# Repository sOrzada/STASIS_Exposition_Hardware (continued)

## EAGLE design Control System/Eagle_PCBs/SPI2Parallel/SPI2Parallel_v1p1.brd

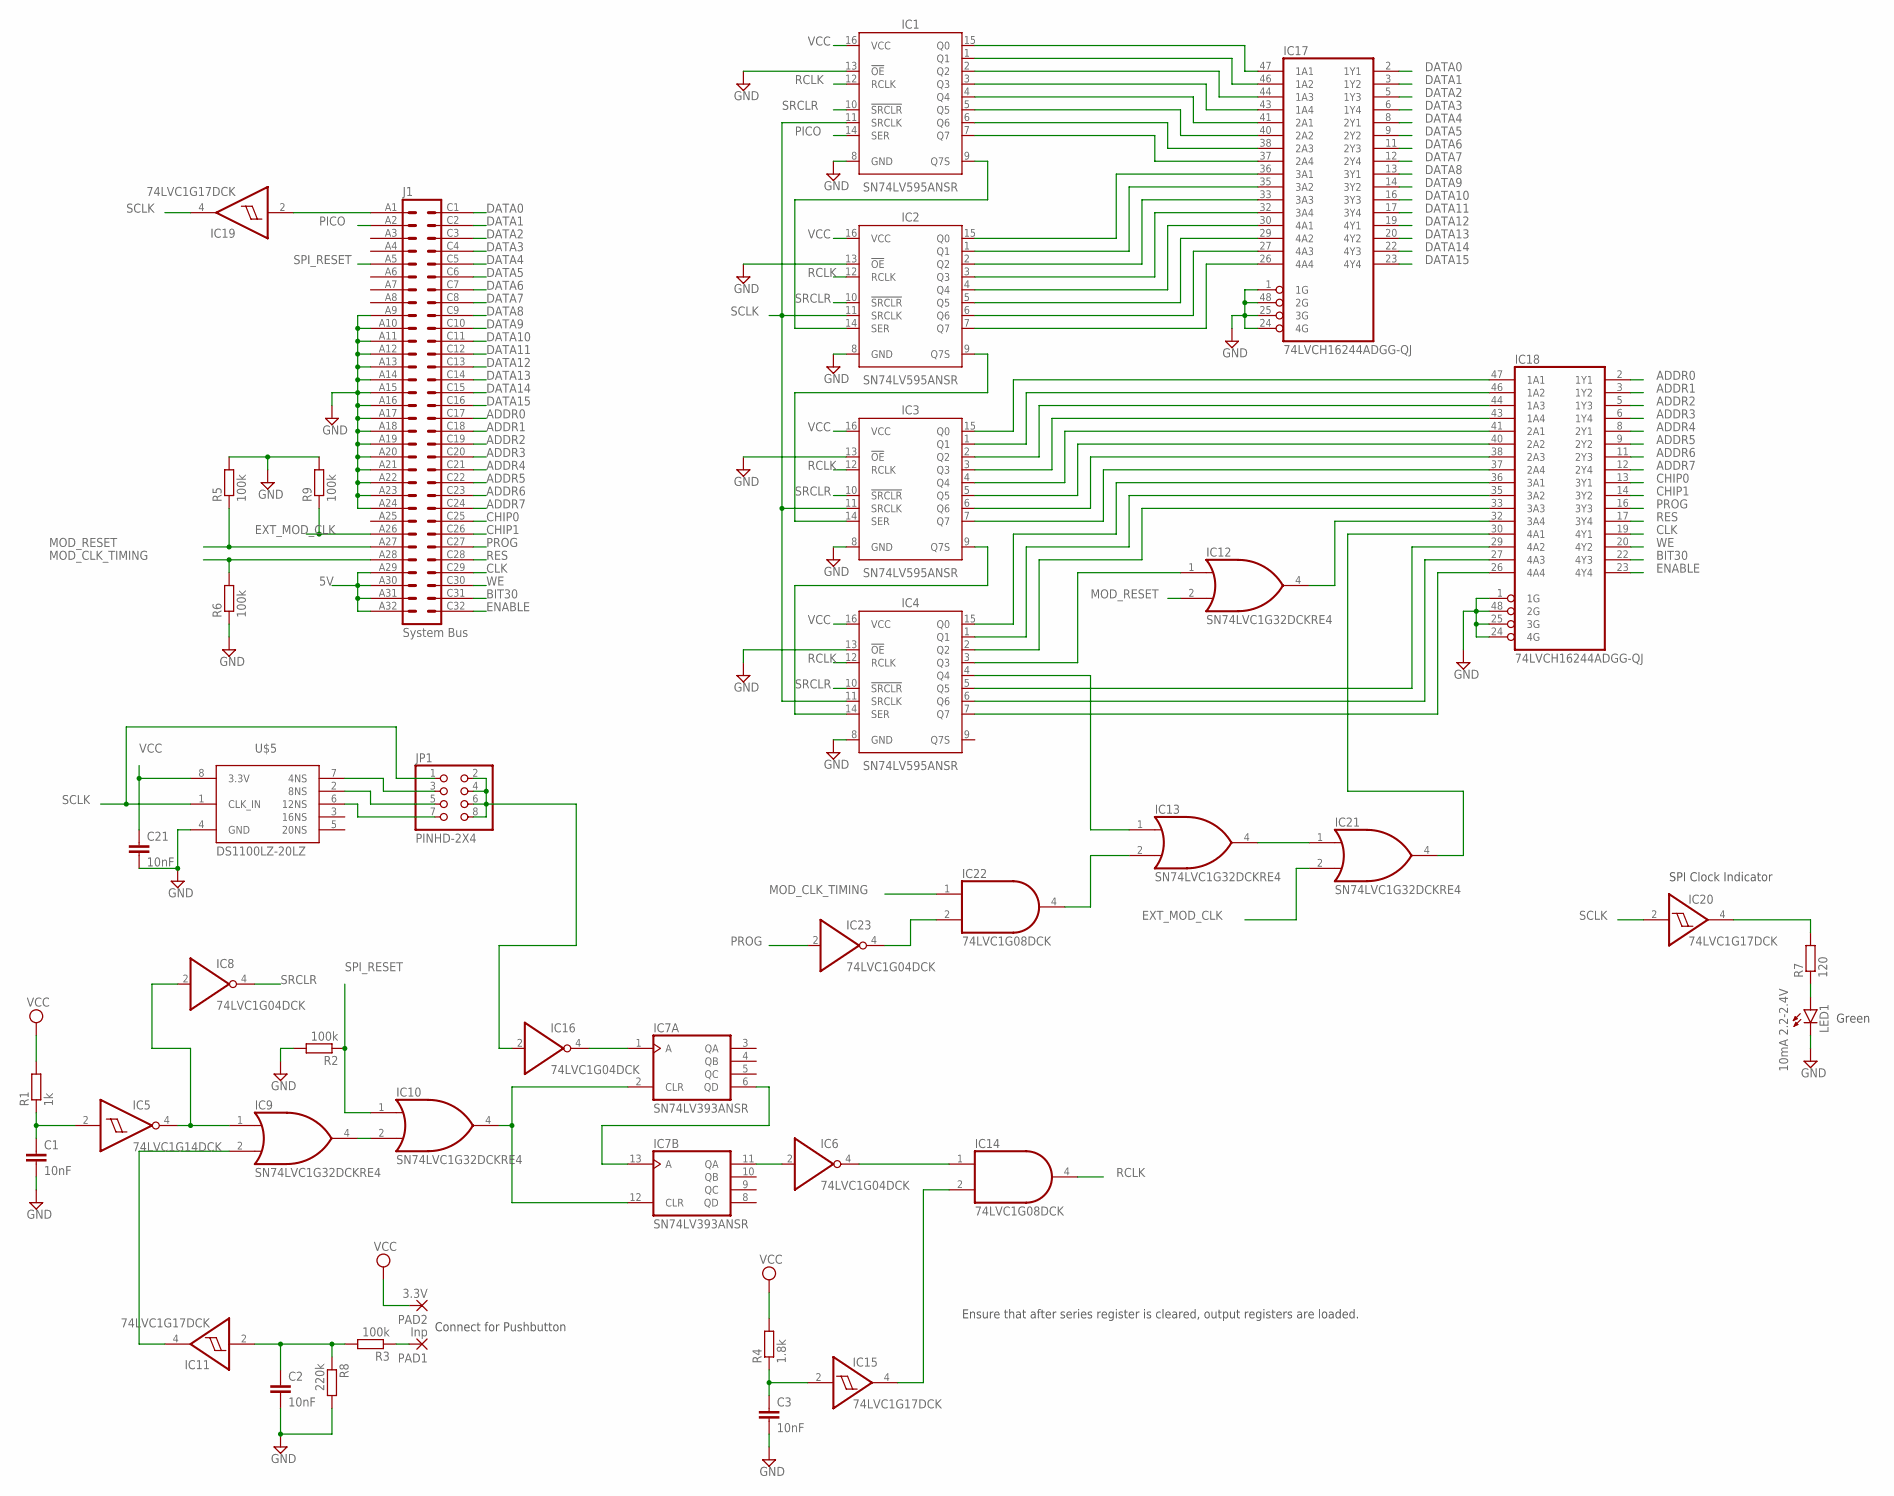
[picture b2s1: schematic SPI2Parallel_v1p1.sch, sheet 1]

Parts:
C1, C2, C3, C21: 10nF; C0603
IC1, IC2, IC3, IC4: SN74LV595ANSR; SOIC127P600X175-16N
IC5: 74LVC1G14DCK; SC70-5
IC6, IC8, IC16, IC23: 74LVC1G04DCK; SC70-5
IC7: SN74LV393ANSR; SO14
IC9, IC10, IC12, IC13, IC21: SN74LVC1G32DCKRE4; SC70-5
IC11, IC15, IC19, IC20: 74LVC1G17DCK; SC70-5
IC14, IC22: 74LVC1G08DCK; SC70-5
IC17, IC18: 74LVCH16244ADGG-QJ; SSOP48DL
J1: System Bus; VG64P
JP1: PINHD-2X4; 2X04
LED1: 10mA 2.2-2.4V; LED3MM
PAD1: Inp; SMD2,54-5,08
PAD2: 3.3V; SMD2,54-5,08
R1: 1k; R0603
R2, R3, R5, R6, R9: 100k; R0603
R4: 1.8k; R0603
R7: 120; R0603
R8: 220k; R0603
U$5: DS1100LZ-20LZ; SO-08

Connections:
5V: J1.A29, J1.A30, J1.A31, J1.A32; also elsewhere on the board
ADDR0: IC18.2 (1Y1), J1.C17
ADDR1: IC18.3 (1Y2), J1.C18
ADDR2: IC18.5 (1Y3), J1.C19
ADDR3: IC18.6 (1Y4), J1.C20
ADDR4: IC18.8 (2Y1), J1.C21
ADDR5: IC18.9 (2Y2), J1.C22
ADDR6: IC18.11 (2Y3), J1.C23
ADDR7: IC18.12 (2Y4), J1.C24
BIT30: IC18.22 (4Y3), J1.C31
CHIP0: IC18.13 (3Y1), J1.C25
CHIP1: IC18.14 (3Y2), J1.C26
CLK: IC18.19 (4Y1), J1.C29
DATA0: IC17.2 (1Y1), J1.C1
DATA1: IC17.3 (1Y2), J1.C2
DATA2: IC17.5 (1Y3), J1.C3
DATA3: IC17.6 (1Y4), J1.C4
DATA4: IC17.8 (2Y1), J1.C5
DATA5: IC17.9 (2Y2), J1.C6
DATA6: IC17.11 (2Y3), J1.C7
DATA7: IC17.12 (2Y4), J1.C8
DATA8: IC17.13 (3Y1), J1.C9
DATA9: IC17.14 (3Y2), J1.C10
DATA10: IC17.16 (3Y3), J1.C11
DATA11: IC17.17 (3Y4), J1.C12
DATA12: IC17.19 (4Y1), J1.C13
DATA13: IC17.20 (4Y2), J1.C14
DATA14: IC17.22 (4Y3), J1.C15
DATA15: IC17.23 (4Y4), J1.C16
ENABLE: IC18.23 (4Y4), J1.C32
EXT_MOD_CLK: IC21.2 (I1), J1.A26, R9.1
GND: C1.2, C2.2, C3.2, C21.2, IC1.8 (GND), IC1.13 (!OE), IC2.8 (GND), IC2.13 (!OE), IC3.8 (GND), IC3.13 (!OE), IC4.8 (GND), IC4.13 (!OE), IC5.3 (GND), IC6.3 (GND), IC7.7 (GND), IC8.3 (GND), IC9.3 (GND), IC10.3 (GND), IC11.3 (GND), IC12.3 (GND), IC13.3 (GND), IC14.3 (GND), IC15.3 (GND), IC16.3 (GND), IC17.1 (1G), IC17.4 (GND), IC17.10 (GND), IC17.15 (GND), IC17.21 (GND), IC17.24 (4G), IC17.25 (3G), IC17.28 (GND), IC17.34 (GND), IC17.39 (GND), IC17.45 (GND), IC17.48 (2G), IC18.1 (1G), IC18.4 (GND), IC18.10 (GND), IC18.15 (GND), IC18.21 (GND), IC18.24 (4G), IC18.25 (3G), IC18.28 (GND), IC18.34 (GND), IC18.39 (GND), IC18.45 (GND), IC18.48 (2G), IC19.3 (GND), IC20.3 (GND), IC21.3 (GND), IC22.3 (GND), IC23.3 (GND), J1.A9, J1.A10, J1.A11, J1.A12, J1.A13, J1.A14, J1.A15, J1.A16, J1.A17, J1.A18, J1.A19, J1.A20, J1.A21, J1.A22, J1.A23, J1.A24, LED1.K (C), R2.2, R5.2, R6.1, R8.2, R9.2, U$5.4 (GND); also elsewhere on the board
MOD_CLK_TIMING: IC22.1 (I0), J1.A28, R6.2
MOD_RESET: IC12.2 (I1), J1.A27, R5.1
unnamed: IC1.9 (Q7S), IC2.14 (SER)
unnamed: IC2.9 (Q7S), IC3.14 (SER)
unnamed: IC3.9 (Q7S), IC4.14 (SER)
unnamed: IC7.6 (QD), IC7.13 (A)
unnamed: IC6.2 (I), IC7.11 (QA)
unnamed: C1.1, IC5.2 (I), R1.1
unnamed: IC7.2 (CLR), IC7.12 (CLR), IC10.4 (O)
unnamed: IC9.4 (O), IC10.2 (I1)
unnamed: IC5.4 (O), IC8.2 (I), IC9.1 (I0)
unnamed: C2.1, IC11.2 (I), R3.2, R8.1
unnamed: IC9.2 (I1), IC11.4 (O)
unnamed: PAD1.1, R3.1
unnamed: IC4.3 (Q3), IC12.1 (I0)
unnamed: IC4.4 (Q4), IC13.1 (I0)
unnamed: IC6.4 (O), IC14.1 (I0)
unnamed: C3.1, IC15.2 (I), R4.1
unnamed: IC14.2 (I1), IC15.4 (O)
unnamed: IC7.1 (A), IC16.4 (O)
unnamed: IC1.15 (Q0), IC17.47 (1A1)
unnamed: IC1.1 (Q1), IC17.46 (1A2)
unnamed: IC1.2 (Q2), IC17.44 (1A3)
unnamed: IC1.3 (Q3), IC17.43 (1A4)
unnamed: IC1.4 (Q4), IC17.41 (2A1)
unnamed: IC1.5 (Q5), IC17.40 (2A2)
unnamed: IC1.6 (Q6), IC17.38 (2A3)
unnamed: IC1.7 (Q7), IC17.37 (2A4)
unnamed: IC2.15 (Q0), IC17.36 (3A1)
unnamed: IC2.1 (Q1), IC17.35 (3A2)
unnamed: IC2.2 (Q2), IC17.33 (3A3)
unnamed: IC2.3 (Q3), IC17.32 (3A4)
unnamed: IC2.4 (Q4), IC17.30 (4A1)
unnamed: IC2.5 (Q5), IC17.29 (4A2)
unnamed: IC2.6 (Q6), IC17.27 (4A3)
unnamed: IC2.7 (Q7), IC17.26 (4A4)
unnamed: IC3.15 (Q0), IC18.47 (1A1)
unnamed: IC3.1 (Q1), IC18.46 (1A2)
unnamed: IC3.2 (Q2), IC18.44 (1A3)
unnamed: IC3.3 (Q3), IC18.43 (1A4)
unnamed: IC3.4 (Q4), IC18.41 (2A1)
unnamed: IC3.5 (Q5), IC18.40 (2A2)
unnamed: IC3.6 (Q6), IC18.38 (2A3)
unnamed: IC3.7 (Q7), IC18.37 (2A4)
unnamed: IC4.15 (Q0), IC18.36 (3A1)
unnamed: IC4.1 (Q1), IC18.35 (3A2)
unnamed: IC4.2 (Q2), IC18.33 (3A3)
unnamed: IC12.4 (O), IC18.32 (3A4)
unnamed: IC18.30 (4A1), IC21.4 (O)
unnamed: IC4.5 (Q5), IC18.29 (4A2)
unnamed: IC4.6 (Q6), IC18.27 (4A3)
unnamed: IC4.7 (Q7), IC18.26 (4A4)
unnamed: IC16.2 (I), JP1.2, JP1.4, JP1.6, JP1.8
unnamed: JP1.7, U$5.6 (12NS)
unnamed: JP1.3, U$5.7 (4NS)
unnamed: JP1.5, U$5.2 (8NS)
unnamed: IC19.2 (I), J1.A1
unnamed: IC13.4 (O), IC21.1 (I0)
unnamed: IC13.2 (I1), IC22.4 (O)
unnamed: IC22.2 (I1), IC23.4 (O)
unnamed: IC20.4 (O), R7.2
unnamed: LED1.A, R7.1
PICO: IC1.14 (SER), J1.A2
PROG: IC18.16 (3Y3), IC23.2 (I), J1.C27
RCLK: IC1.12 (RCLK), IC2.12 (RCLK), IC3.12 (RCLK), IC4.12 (RCLK), IC14.4 (O)
RES: IC18.17 (3Y4), J1.C28
SCLK: IC1.11 (SRCLK), IC2.11 (SRCLK), IC3.11 (SRCLK), IC4.11 (SRCLK), IC19.4 (O), IC20.2 (I), JP1.1, U$5.1 (CLK_IN)
SPI_RESET: IC10.1 (I0), J1.A5, R2.1
SRCLR: IC1.10 (!SRCLR), IC2.10 (!SRCLR), IC3.10 (!SRCLR), IC4.10 (!SRCLR), IC8.4 (O)
VCC: C21.1, IC1.16 (VCC), IC2.16 (VCC), IC3.16 (VCC), IC4.16 (VCC), IC5.5 (VCC), IC6.5 (VCC), IC7.14 (VCC), IC8.5 (VCC), IC9.5 (VCC), IC10.5 (VCC), IC11.5 (VCC), IC12.5 (VCC), IC13.5 (VCC), IC14.5 (VCC), IC15.5 (VCC), IC16.5 (VCC), IC17.7 (VCC), IC17.18 (VCC), IC17.31 (VCC), IC17.42 (VCC), IC18.7 (VCC), IC18.18 (VCC), IC18.31 (VCC), IC18.42 (VCC), IC19.5 (VCC), IC20.5 (VCC), IC21.5 (VCC), IC22.5 (VCC), IC23.5 (VCC), PAD2.1, R1.2, R4.2, U$5.8 (3.3V); also elsewhere on the board
WE: IC18.20 (4Y2), J1.C30

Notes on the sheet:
Connect for Pushbutton
Ensure that after series register is cleared, output registers are loaded.
Green
SPI Clock Indicator

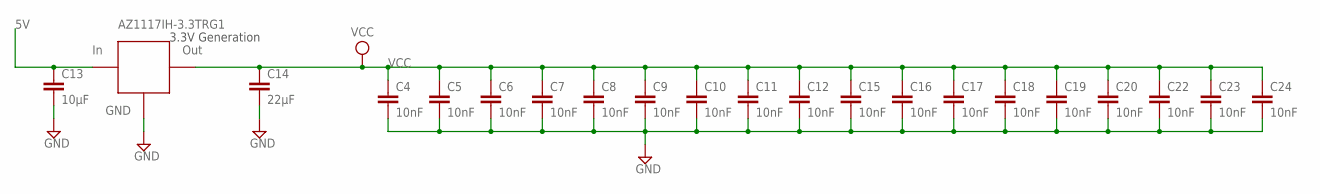
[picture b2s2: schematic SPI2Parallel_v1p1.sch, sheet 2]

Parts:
C4, C5, C6, C7, C8, C9, C10, C11, C12, C15, C16, C17, C18, C19, C20, C22, C23, C24: 10nF; C0603
C13: 10µF; C1206
C14: 22µF; C1206
U$9: AZ1117IH-3.3TRG1; SOT223

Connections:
5V: C13.1, U$9.3 (IN); also elsewhere on the board
GND: C4.2, C5.2, C6.2, C7.2, C8.2, C9.2, C10.2, C11.2, C12.2, C13.2, C14.2, C15.2, C16.2, C17.2, C18.2, C19.2, C20.2, C22.2, C23.2, C24.2, U$9.1 (GND); also elsewhere on the board
VCC: C4.1, C5.1, C6.1, C7.1, C8.1, C9.1, C10.1, C11.1, C12.1, C14.1, C15.1, C16.1, C17.1, C18.1, C19.1, C20.1, C22.1, C23.1, C24.1, U$9.2 (VCC), U$9.4 (VCC); also elsewhere on the board

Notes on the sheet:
3.3V Generation

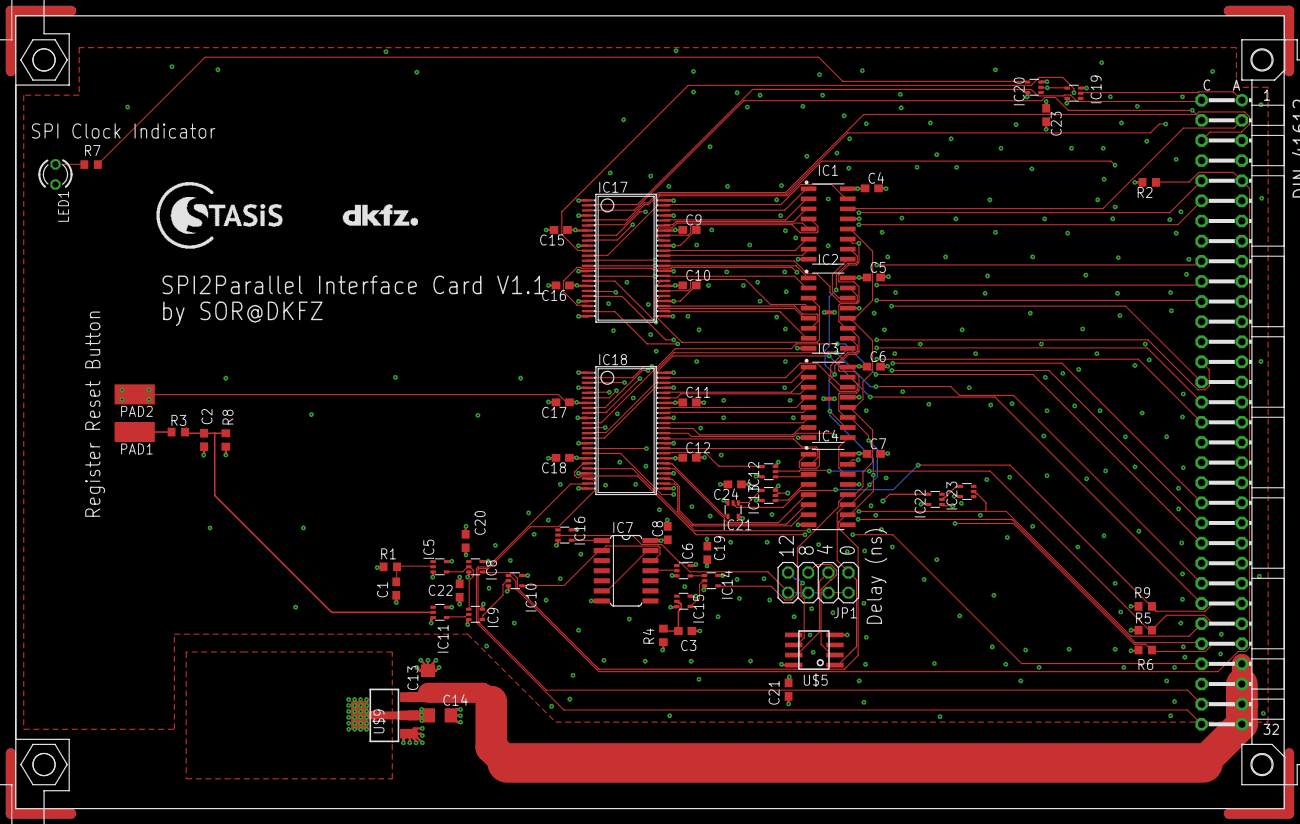
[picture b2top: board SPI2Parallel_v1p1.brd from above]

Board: 4 copper layers, 160.0 x 100.0 mm, 65 parts (0 on the bottom side), 103 nets.

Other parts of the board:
U$1: LOGO_STASIS
U$2: LOGO_DKFZ

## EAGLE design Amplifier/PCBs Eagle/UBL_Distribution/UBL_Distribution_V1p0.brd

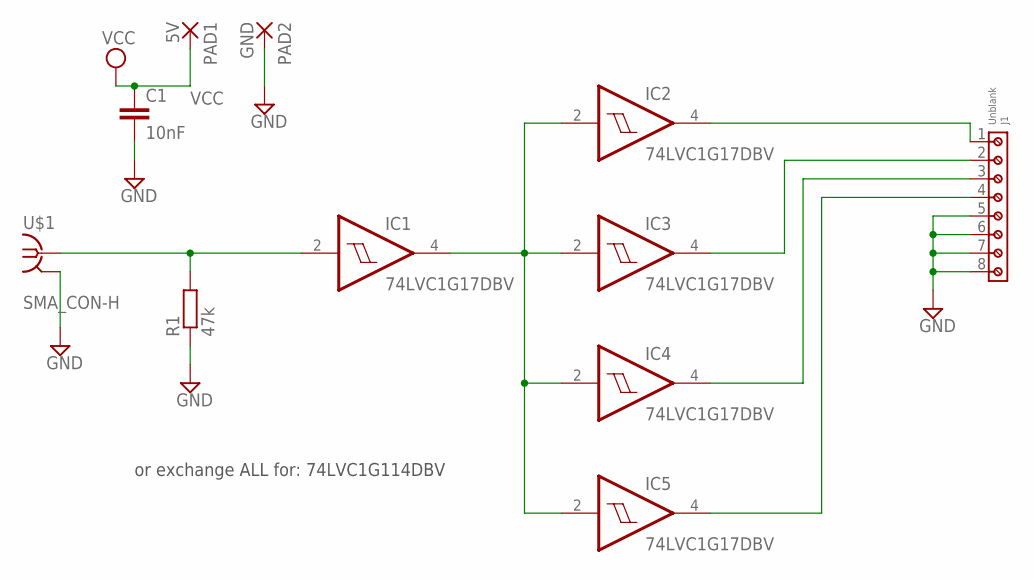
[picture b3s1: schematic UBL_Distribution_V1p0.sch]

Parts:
C1: 10nF; C0805
IC1, IC2, IC3, IC4, IC5: 74LVC1G17DBV; SOT23-5
J1: Unblank; 691210910008
PAD1: 5V; SMD2,54-5,08
PAD2: GND; SMD2,54-5,08
R1: 47k; R0805
U$1: SMA_CON-H; BU-SMA-H

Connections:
GND: C1.2, IC1.3 (GND), IC2.3 (GND), IC3.3 (GND), IC4.3 (GND), IC5.3 (GND), J1.5, J1.6, J1.7, J1.8, PAD2.1, R1.1, U$1.2 (GND), U$1.3 (GND), U$1.4 (GND), U$1.5 (GND)
unnamed: IC1.2 (I), R1.2, U$1.1
unnamed: IC1.4 (O), IC2.2 (I), IC3.2 (I), IC4.2 (I), IC5.2 (I)
unnamed: IC2.4 (O), J1.1
unnamed: IC3.4 (O), J1.2
unnamed: IC4.4 (O), J1.3
unnamed: IC5.4 (O), J1.4
VCC: C1.1, IC1.5 (VCC), IC2.5 (VCC), IC3.5 (VCC), IC4.5 (VCC), IC5.5 (VCC), PAD1.1

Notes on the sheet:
or exchange ALL for: 74LVC1G114DBV

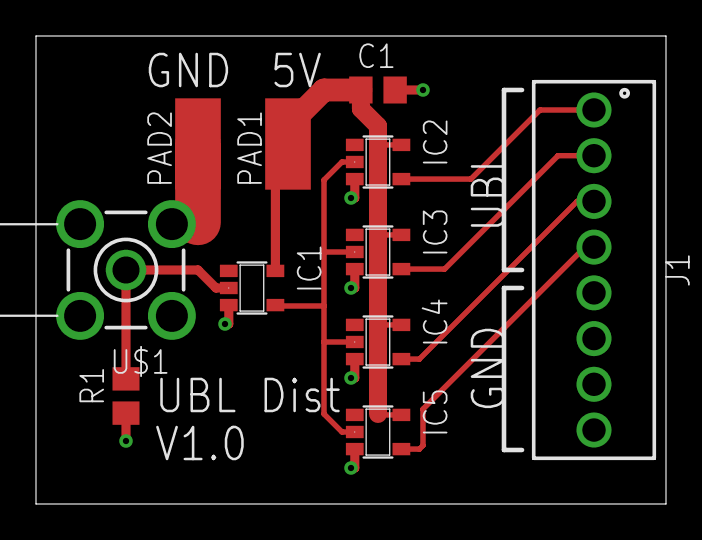
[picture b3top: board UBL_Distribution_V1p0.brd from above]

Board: 2 copper layers, 35.0 x 26.0 mm, 11 parts (0 on the bottom side), 8 nets.

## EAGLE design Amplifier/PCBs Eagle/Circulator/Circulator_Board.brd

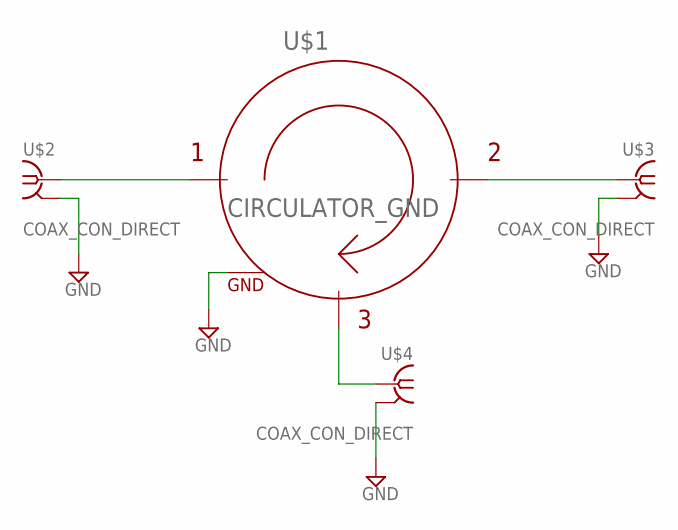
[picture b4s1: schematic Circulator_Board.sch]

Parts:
U$1: CIRCULATOR_GND; JCD0126T0130LC100
U$2, U$3, U$4: COAX_CON_DIRECT; COAX.141

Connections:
GND: U$1.P$1 (P$GND), U$1.P$2 (P$GND), U$1.P$3 (P$GND), U$1.P$4 (P$GND), U$2.P$2 (GND), U$3.P$2 (GND), U$4.P$2 (GND)
unnamed: U$1.P$IN, U$2.P$1 (1)
unnamed: U$1.P$OUT, U$3.P$1 (1)
unnamed: U$1.P$LOAD, U$4.P$1 (1)

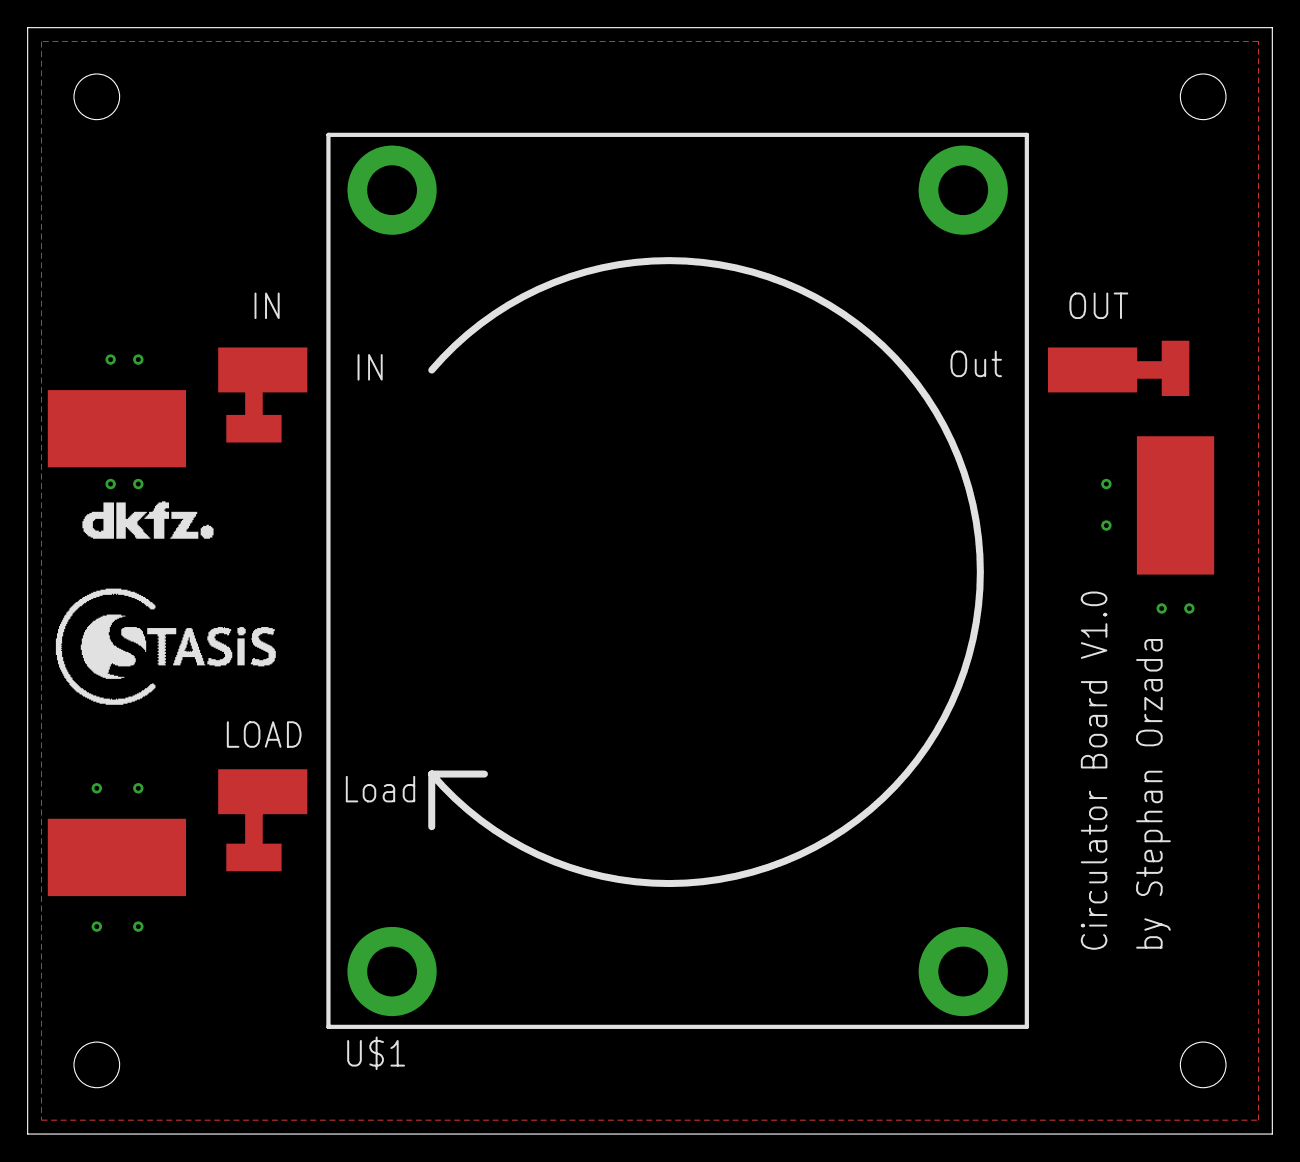
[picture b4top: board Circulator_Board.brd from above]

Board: 2 copper layers, 90.0 x 80.0 mm, 6 parts (0 on the bottom side), 4 nets.

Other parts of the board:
U$5: LOGO_DKFZ
U$6: LOGO_STASIS

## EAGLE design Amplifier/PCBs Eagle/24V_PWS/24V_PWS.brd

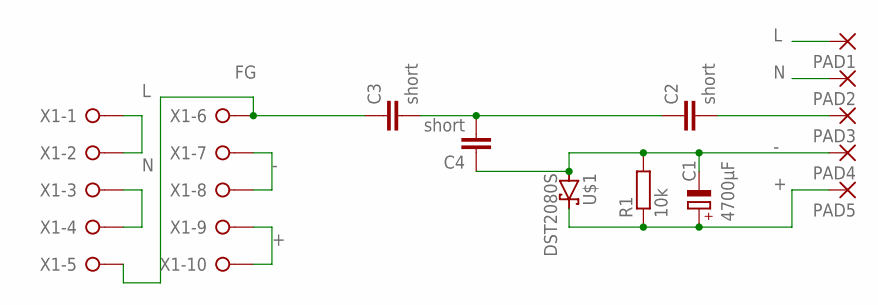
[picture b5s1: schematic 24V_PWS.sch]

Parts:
C1: 4700µF; E7,5-18
C2, C3, C4: short; C1206
PAD1, PAD2, PAD3, PAD4, PAD5: SMD5; SMD2,54-5,08
R1: 10k; R2012
U$1: DST2080S; TO-277B
X1: W237-10P

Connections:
+: C1.+, PAD5.1, R1.1, U$1.P$1 (C), X1.9, X1.10
-: C1.-, C4.1, PAD4.1, R1.2, U$1.P$2 (A), U$1.P$3 (A), X1.7, X1.8
FG: C3.1, X1.5, X1.6
L: PAD1.1, X1.1, X1.2
N: PAD2.1, X1.3, X1.4
unnamed: C2.2, PAD3.1
unnamed: C2.1, C3.2, C4.2

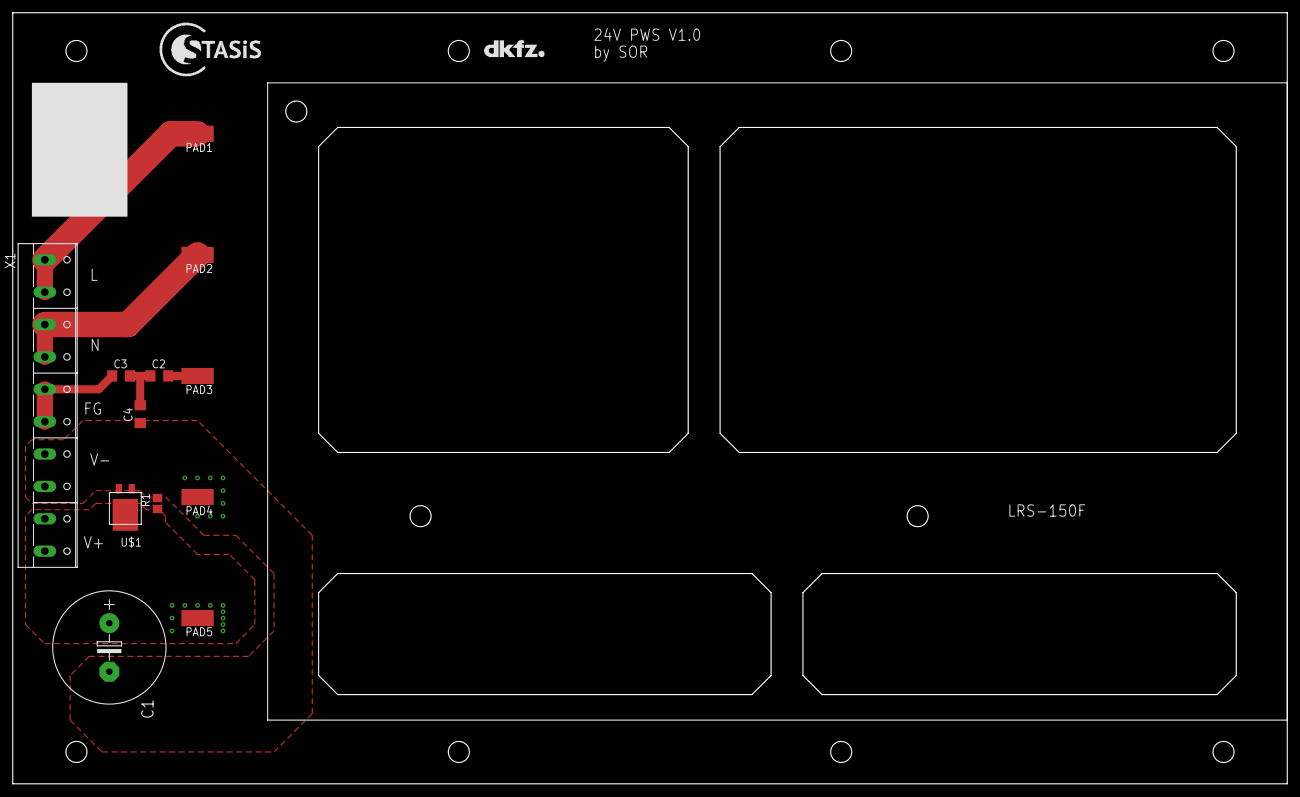
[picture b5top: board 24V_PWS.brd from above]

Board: 2 copper layers, 200.0 x 121.0 mm, 14 parts (0 on the bottom side), 7 nets.

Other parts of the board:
U$2: LOGO_STASIS
U$3: LOGO_DKFZ

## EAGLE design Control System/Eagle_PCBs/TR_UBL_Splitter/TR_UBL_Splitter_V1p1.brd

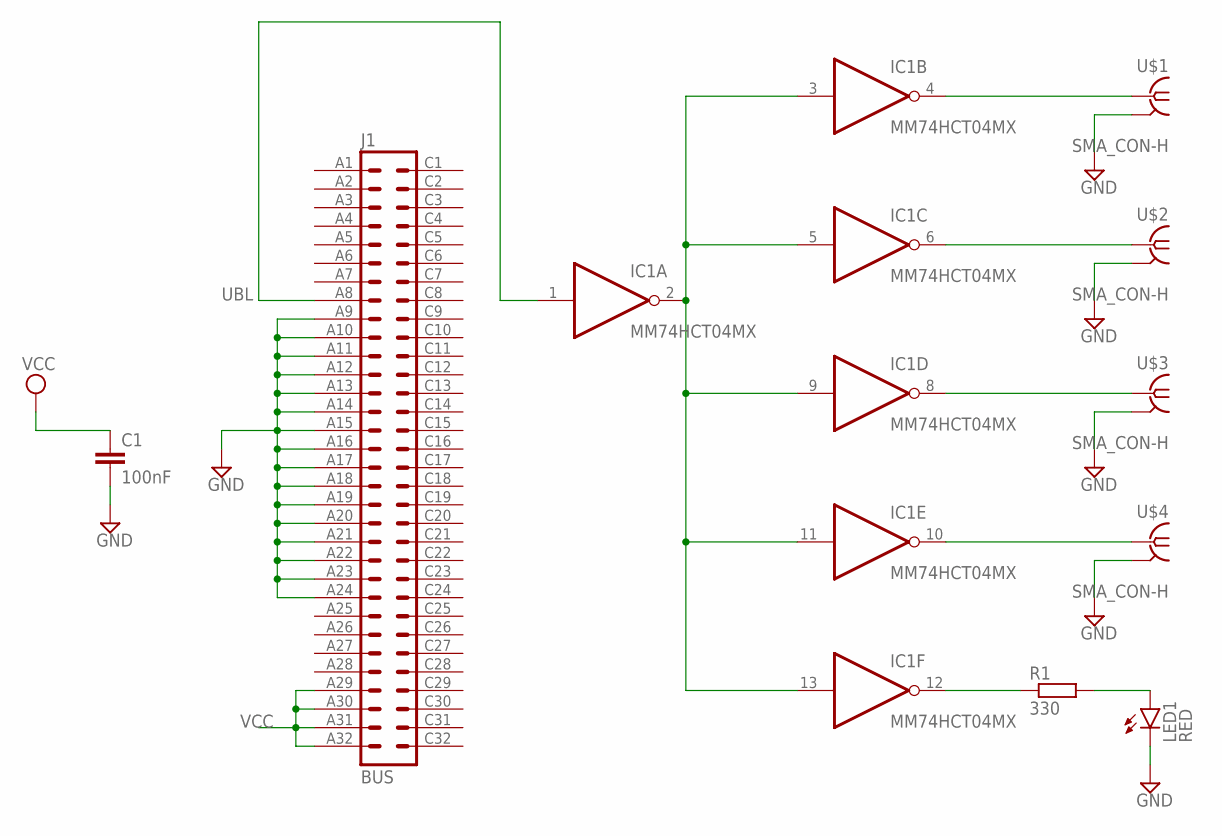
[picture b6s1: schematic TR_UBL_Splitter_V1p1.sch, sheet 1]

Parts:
C1: 100nF; C0603
IC1: MM74HCT04MX; SO14
J1: BUS; VG64P
LED1: RED; LED3MM
R1: 330; R0603
U$1, U$2, U$3, U$4: SMA_CON-H; BU-SMA-H

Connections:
GND: C1.2, IC1.7 (GND), J1.A9, J1.A10, J1.A11, J1.A12, J1.A13, J1.A14, J1.A15, J1.A16, J1.A17, J1.A18, J1.A19, J1.A20, J1.A21, J1.A22, J1.A23, J1.A24, LED1.K (C), U$1.2 (GND), U$1.3 (GND), U$1.4 (GND), U$1.5 (GND), U$2.2 (GND), U$2.3 (GND), U$2.4 (GND), U$2.5 (GND), U$3.2 (GND), U$3.3 (GND), U$3.4 (GND), U$3.5 (GND), U$4.2 (GND), U$4.3 (GND), U$4.4 (GND), U$4.5 (GND)
unnamed: IC1.2 (O), IC1.3 (I), IC1.5 (I), IC1.9 (I), IC1.11 (I), IC1.13 (I)
unnamed: IC1.4 (O), U$1.1
unnamed: LED1.A, R1.2
unnamed: IC1.6 (O), U$2.1
unnamed: IC1.12 (O), R1.1
unnamed: IC1.8 (O), U$3.1
unnamed: IC1.10 (O), U$4.1
UBL: IC1.1 (I), J1.A8
VCC: C1.1, IC1.14 (VCC), J1.A29, J1.A30, J1.A31, J1.A32

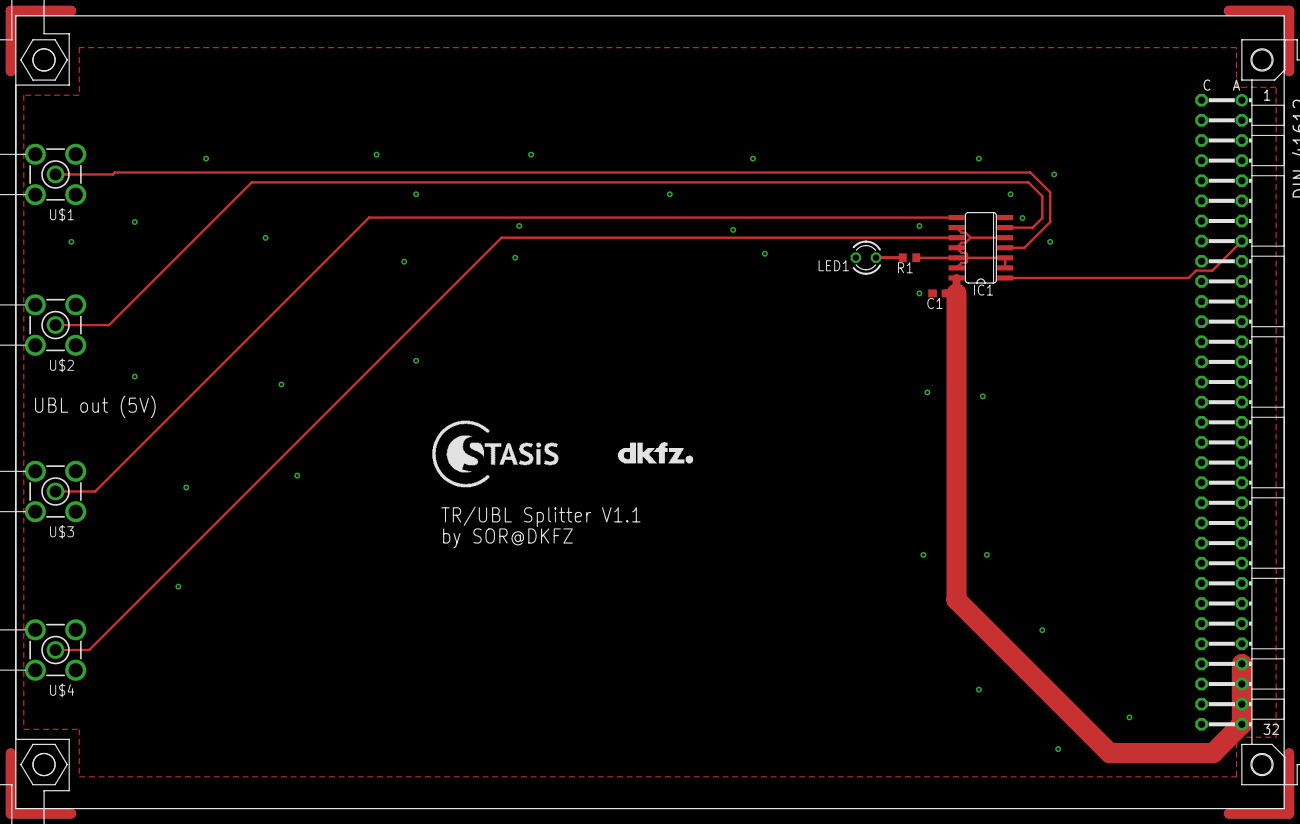
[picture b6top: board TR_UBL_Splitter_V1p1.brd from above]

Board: 2 copper layers, 160.0 x 100.0 mm, 11 parts (0 on the bottom side), 10 nets.

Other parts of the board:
U$5: LOGO_STASIS
U$6: LOGO_DKFZ

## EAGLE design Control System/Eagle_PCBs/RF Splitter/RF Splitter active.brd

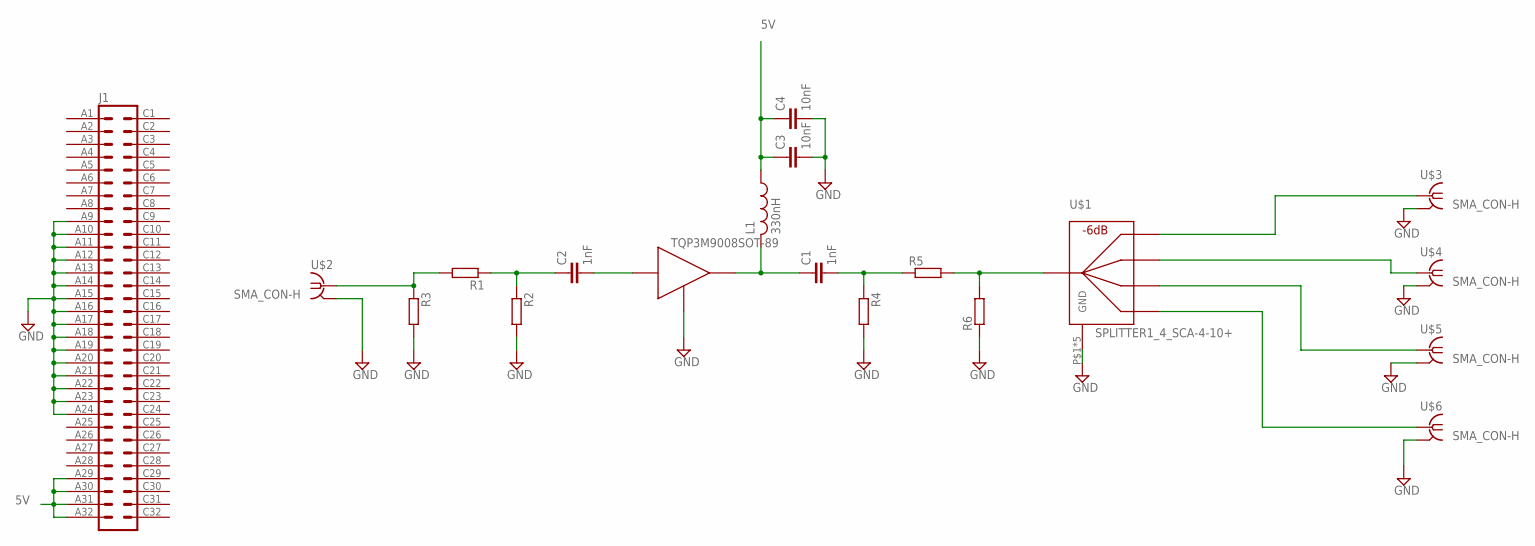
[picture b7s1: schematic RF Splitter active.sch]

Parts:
C1, C2: 1nF; C0603
C3, C4: 10nF; C0603
J1: VG64P
L1: 330nH; L2012C
R1, R2, R3, R4, R5, R6: R-EU_R0603; R0603
U$1: SPLITTER1_4_SCA-4-10+; SCA-4-10+
U$2, U$3, U$4, U$5, U$6: SMA_CON-H; BU-SMA-H
U$7: TQP3M9008SOT-89; SOT89

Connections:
5V: C3.1, C4.1, J1.A29, J1.A30, J1.A31, J1.A32, L1.1
GND: C3.2, C4.2, J1.A9, J1.A10, J1.A11, J1.A12, J1.A13, J1.A14, J1.A15, J1.A16, J1.A17, J1.A18, J1.A19, J1.A20, J1.A21, J1.A22, J1.A23, J1.A24, R2.2, R3.2, R4.2, R6.1, U$1.P$1 (GND), U$1.P$2 (GND), U$1.P$4 (GND), U$1.P$5 (GND), U$1.P$8 (GND), U$2.2 (GND), U$2.3 (GND), U$2.4 (GND), U$2.5 (GND), U$3.2 (GND), U$3.3 (GND), U$3.4 (GND), U$3.5 (GND), U$4.2 (GND), U$4.3 (GND), U$4.4 (GND), U$4.5 (GND), U$5.2 (GND), U$5.3 (GND), U$5.4 (GND), U$5.5 (GND), U$6.2 (GND), U$6.3 (GND), U$6.4 (GND), U$6.5 (GND), U$7.2 (GND), U$7.2@1 (GND)
unnamed: C2.2, U$7.1 (IN)
unnamed: U$1.P$6, U$3.1
unnamed: U$1.P$7, U$4.1
unnamed: U$1.P$9, U$5.1
unnamed: U$1.P$10, U$6.1
unnamed: C1.1, L1.2, U$7.3 (OUT)
unnamed: C1.2, R4.1, R5.1
unnamed: R5.2, R6.2, U$1.P$3
unnamed: R1.2, R3.1, U$2.1
unnamed: C2.1, R1.1, R2.1

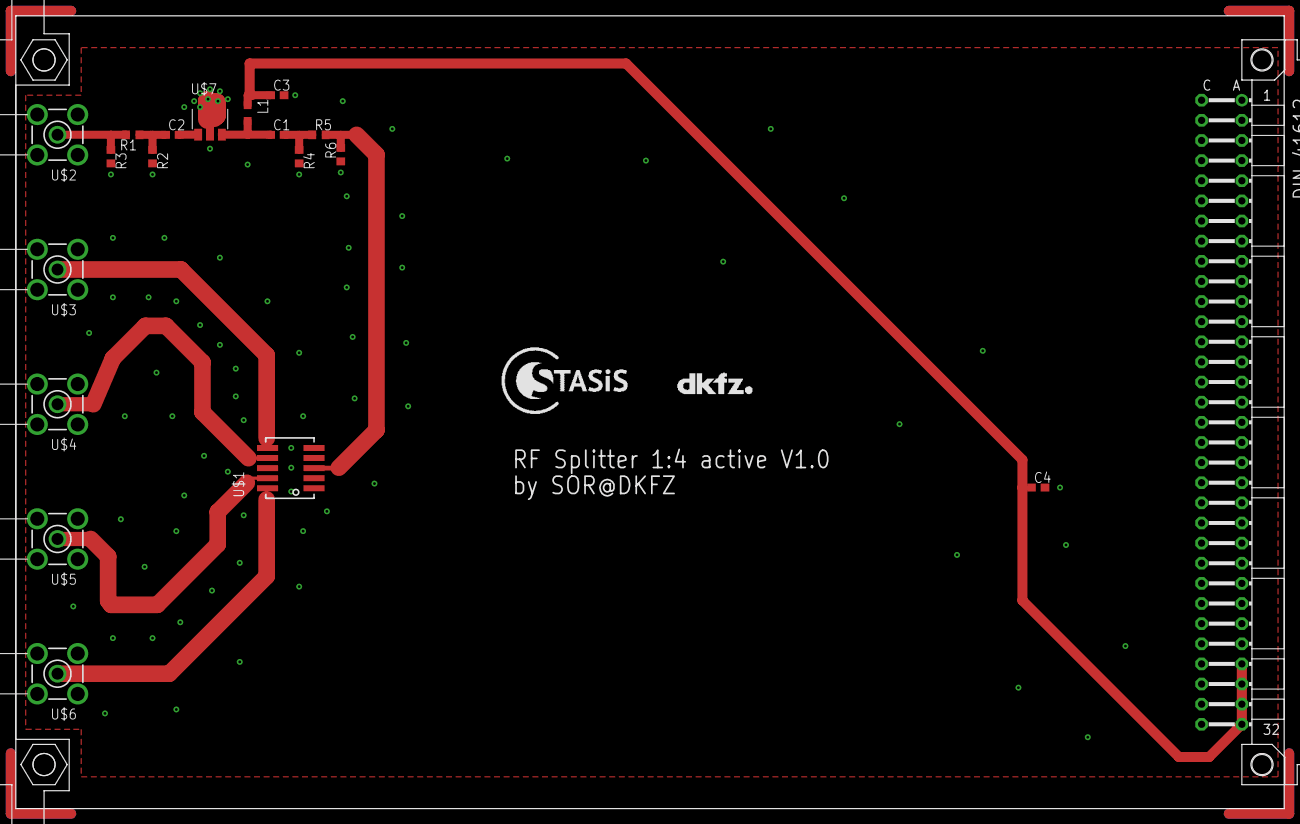
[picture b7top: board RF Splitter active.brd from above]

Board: 2 copper layers, 160.0 x 100.0 mm, 21 parts (0 on the bottom side), 12 nets.

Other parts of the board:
U$8: LOGO_STASIS
U$9: LOGO_DKFZ

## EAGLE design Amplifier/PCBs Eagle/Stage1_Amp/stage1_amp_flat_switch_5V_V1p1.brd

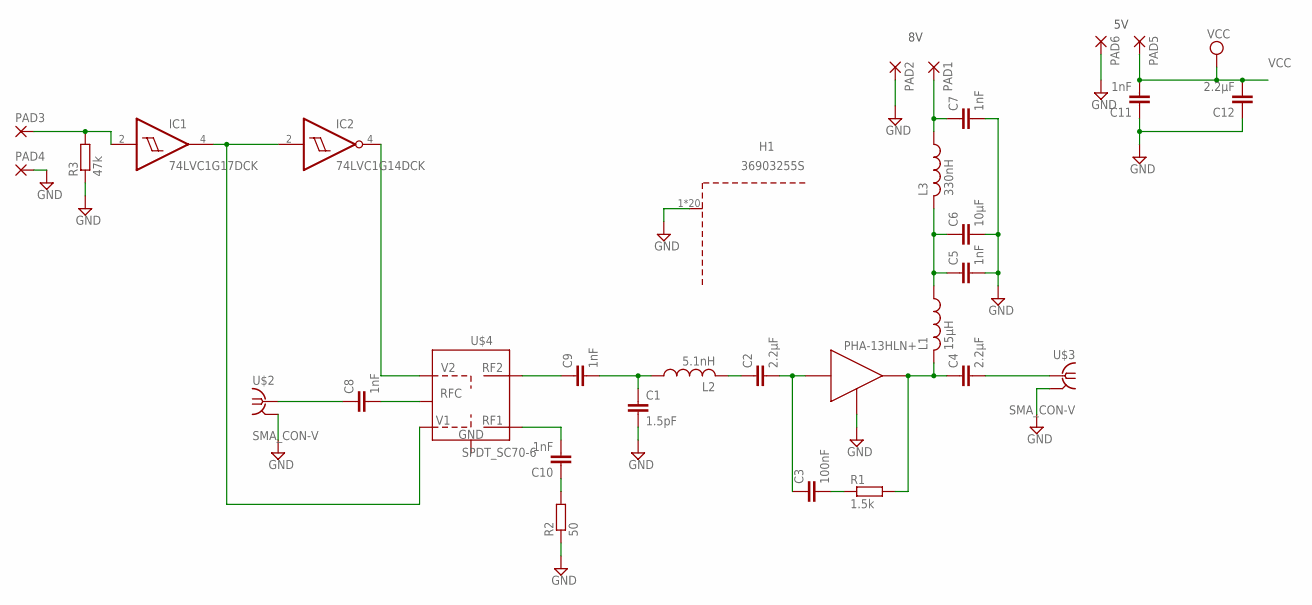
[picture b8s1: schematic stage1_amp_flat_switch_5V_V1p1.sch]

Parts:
C1: 1.5pF; C0402
C2, C4, C12: 2.2µF; C0402
C3: 100nF; C0402
C5, C7, C8, C9, C10, C11: 1nF; C0402
C6: 10µF; C0805
H1: 36903255S; WE-SHC_ONE-PIECE_36903255S
IC1: 74LVC1G17DCK; SC70-5
IC2: 74LVC1G14DCK; SC70-5
L1: 15µH; L3225M
L2: 5.1nH; L2012C
L3: 330nH; L3225M
PAD1, PAD2, PAD3, PAD4, PAD5, PAD6: SMD5; SMD2,54-5,08
R1: 1.5k; R0402
R2: 50; R0402
R3: 47k; R0805
U$1: PHA-13HLN+; SOT89
U$2, U$3: SMA_CON-V; BU-SMA-V
U$4: SPDT_SC70-6; SC70-6

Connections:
GND: C1.2, C5.2, C6.2, C7.2, C11.1, C12.1, H1.1, H1.2, H1.3, H1.4, H1.5, H1.6, H1.7, H1.8, H1.9, H1.10, H1.11, H1.12, H1.13, H1.14, H1.15, H1.16, H1.17, H1.18, H1.19, H1.20, IC1.3 (GND), IC2.3 (GND), PAD2.1, PAD4.1, PAD6.1, R2.1, R3.1, U$1.2 (GND), U$1.2@1 (GND), U$2.2 (GND), U$2.3 (GND), U$2.4 (GND), U$2.5 (GND), U$3.2 (GND), U$3.3 (GND), U$3.4 (GND), U$3.5 (GND)
unnamed: C2.1, L2.2
unnamed: C2.2, C3.1, U$1.1 (IN)
unnamed: C4.1, L1.2, R1.2, U$1.3 (OUT)
unnamed: C1.1, C9.2, L2.1
unnamed: C3.2, R1.1
unnamed: C4.2, U$3.1
unnamed: C5.1, C6.1, L1.1, L3.2
unnamed: C7.1, L3.1, PAD1.1
unnamed: C8.2, U$4.5 (RFC)
unnamed: C8.1, U$2.1
unnamed: C9.1, U$4.3 (RF2)
unnamed: C10.2, U$4.1 (RF1)
unnamed: C10.1, R2.2
unnamed: IC1.4 (O), IC2.2 (I), U$4.6 (V1)
unnamed: IC2.4 (O), U$4.4 (V2)
unnamed: IC1.2 (I), PAD3.1, R3.2
VCC: C11.2, C12.2, IC1.5 (VCC), IC2.5 (VCC), PAD5.1

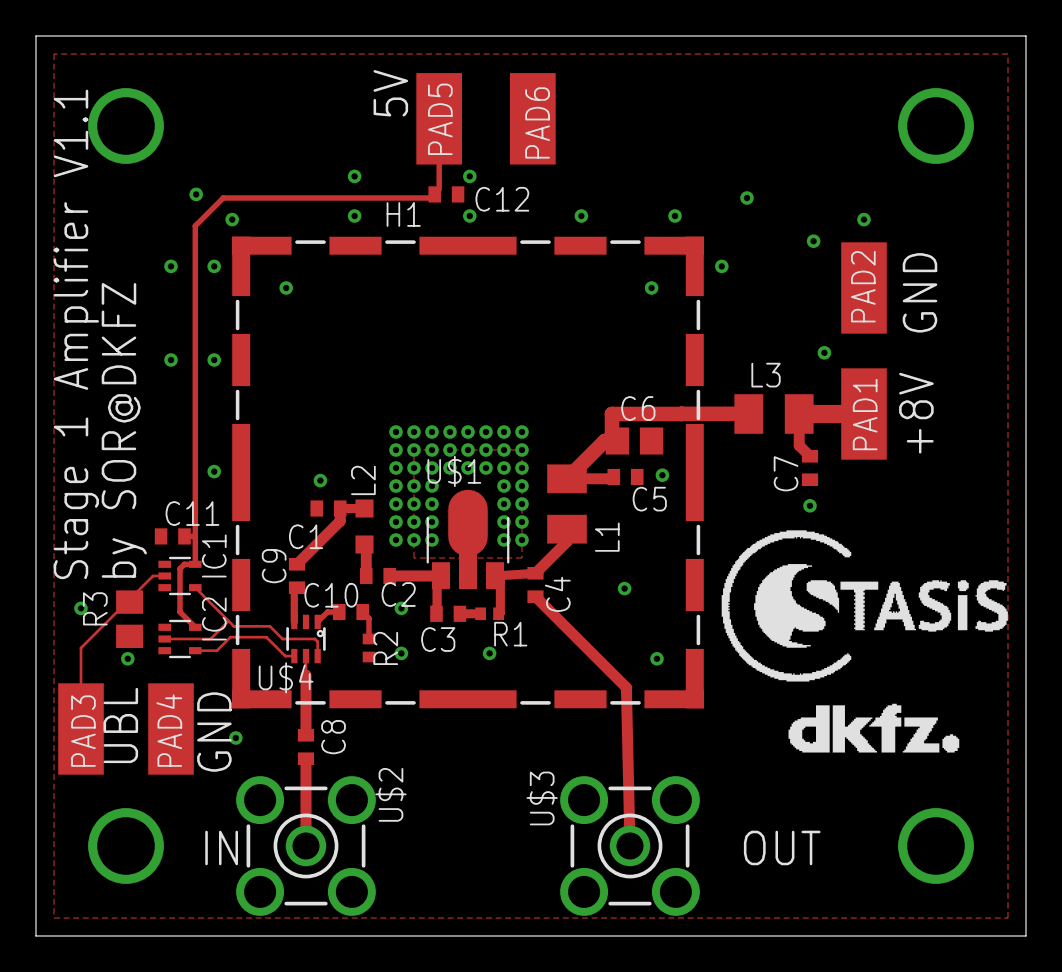
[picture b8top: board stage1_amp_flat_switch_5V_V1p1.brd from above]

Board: 2 copper layers, 55.0 x 50.0 mm, 33 parts (0 on the bottom side), 18 nets.

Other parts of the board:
U$5: LOGO_DKFZ
U$6: LOGO_STASIS

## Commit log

2025-02-12 Upload Array data and Main Documentation Document.
2025-02-12 Upload PCBs and Housing
2025-02-12 Deleted Backup of Documentation Document.
2025-02-12 Added Name to Readme
2025-02-12 Changed Readme
2025-02-12 Added Spice Simulations
    -HPA
    -2nd stage amplifier
    -Voltage Control
2025-02-12 Create LICENSE
    Added License
2025-02-12 Create Disclaimer.txt
    Created disclaimer.
2025-02-12 Closed KiCad, which changed a backup file.
2025-02-17 Expanded Documentation Included warnings Included description of GUI (not finished yet).
2025-03-19 Updated Calibration Changed the way the calibration should be done and changed the documentation accordingly.
2025-09-16 Added Fusion360 file for array housing
2025-09-16 Added Partlist
    Added partlist with prices at time of purchase.
2025-09-30 Added more explanation to readme
